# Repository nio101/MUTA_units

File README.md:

# MUTA_units
An open source home automation solution for hobbyists and makers

## customizing the firmwares before flashing

In the **MPLAB IPE**, activate *Setting/advanced mode*, open the firmware/.hex file you want to customize, and then select *View/show memory*.
On the *Operate* tab, you'll have a memory view window. Skip to the end of the memory and you fill view the constants you can edit inline before flashing:
* static_encryption_key @ 0x01FFEC (8 bytes)
* make/model @ 0x01FFF4 (2 bytes)
* unit_uid @ 0x01FFF6 (2 bytes)
You can then use the *view/fill memory* dialog to modify those values and check the modifications on the memory view afterwards.
*important: due to Endianness, the first and second bytes are swapped for each memory value, so you should input for example 0x0201@0x01FFF4 to get a 01 model and a 02 make*
*remark: This manual process could be done in a much easier way with the hexmate util, but my first tries weren't successfull and I couldn't spend more time on it.*

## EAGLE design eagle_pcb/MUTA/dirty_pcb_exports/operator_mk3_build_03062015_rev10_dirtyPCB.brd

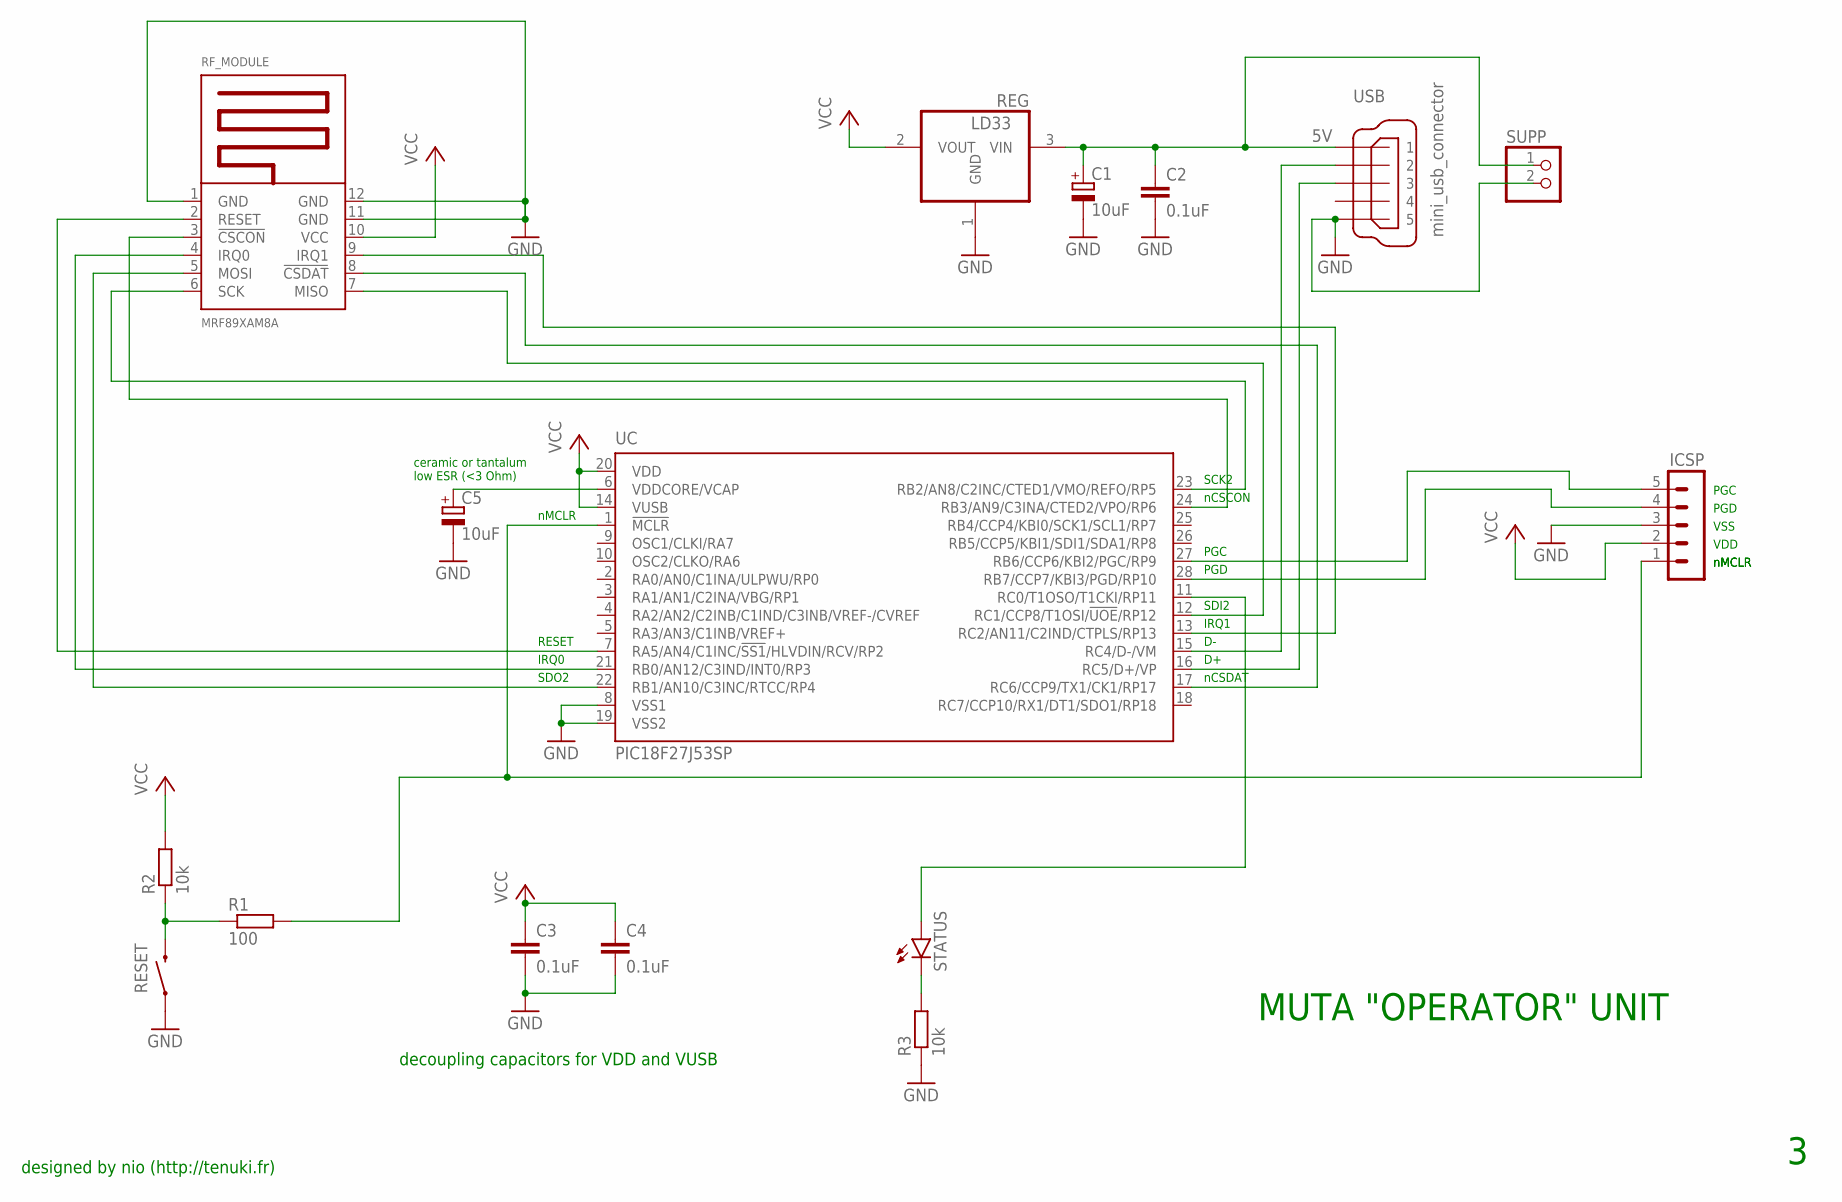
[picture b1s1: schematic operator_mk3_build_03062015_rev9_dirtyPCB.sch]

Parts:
C1: 10uF; TT5D6
C2, C3, C4: 0.1uF; C050-025X075
C5: 10uF; C/6032-28R
ICSP: MA05-1
R1: 100; 0207/10
R2: 10k; 0207/10
R3: 10k; 0207/2V
REG: LD33; SOT223; MPN LD33
RESET: SWITCH-MOMENTARY-2PTH; TACTILE-PTH
RF_MODULE: MRF89XAM8A; MRF89XAMXA
STATUS: LED5MM
SUPP: PINHD-1X2; 1X02
UC: PIC18F27J53SP; DIL28-3
USB: mini_usb_connector; UX60-MB-5ST

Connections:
5V: C1.+, C2.1, REG.3 (VIN), SUPP.1, USB.1
GND: C1.-, C2.2, C3.2, C4.2, C5.-, ICSP.3, R3.1, REG.1 (GND), RESET.1, RF_MODULE.1 (GND), RF_MODULE.11 (GND), RF_MODULE.12 (GND), SUPP.2, UC.8 (VSS1), UC.19 (VSS2), USB.5
unnamed: UC.15 (RC4/D-/VM), USB.2
unnamed: UC.16 (RC5/D+/VP), USB.3
unnamed: ICSP.1, R1.2, UC.1 (!MCLR)
unnamed: C5.+, UC.6 (VDDCORE/VCAP)
unnamed: R1.1, R2.1, RESET.3 (2)
unnamed: ICSP.4, UC.28 (RB7/CCP7/KBI3/PGD/RP10)
unnamed: ICSP.5, UC.27 (RB6/CCP6/KBI2/PGC/RP9)
unnamed: RF_MODULE.2 (RESET), UC.7 (RA5/AN4/C1INC/!SS1!/HLVDIN/RCV/RP2)
unnamed: RF_MODULE.6 (SCK), UC.23 (RB2/AN8/C2INC/CTED1/VMO/REFO/RP5)
unnamed: R3.2, STATUS.K (C)
unnamed: STATUS.A, UC.11 (RC0/T1OSO/T1CKI/RP11)
unnamed: RF_MODULE.7 (MISO), UC.12 (RC1/CCP8/T1OSI/!UOE!/RP12)
unnamed: RF_MODULE.3 (!CSCON), UC.24 (RB3/AN9/C3INA/CTED2/VPO/RP6)
unnamed: RF_MODULE.5 (MOSI), UC.22 (RB1/AN10/C3INC/RTCC/RP4)
unnamed: RF_MODULE.4 (IRQ0), UC.21 (RB0/AN12/C3IND/INT0/RP3)
unnamed: RF_MODULE.9 (IRQ1), UC.13 (RC2/AN11/C2IND/CTPLS/RP13)
unnamed: RF_MODULE.8 (!CSDAT), UC.17 (RC6/CCP9/TX1/CK1/RP17)
VCC: C3.1, C4.1, ICSP.2, R2.2, REG.2 (VOUT), RF_MODULE.10 (VCC), UC.14 (VUSB), UC.20 (VDD)

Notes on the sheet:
MUTA "OPERATOR" UNIT
decoupling capacitors for VDD and VUSB
ceramic or tantalum low ESR (<3 Ohm)
nMCLR
VDD
VSS
PGD
PGC
SCK2
SDI2
SDO2
IRQ1
IRQ0
nCSDAT
nCSCON
RESET
designed by nio (http://tenuki.fr)

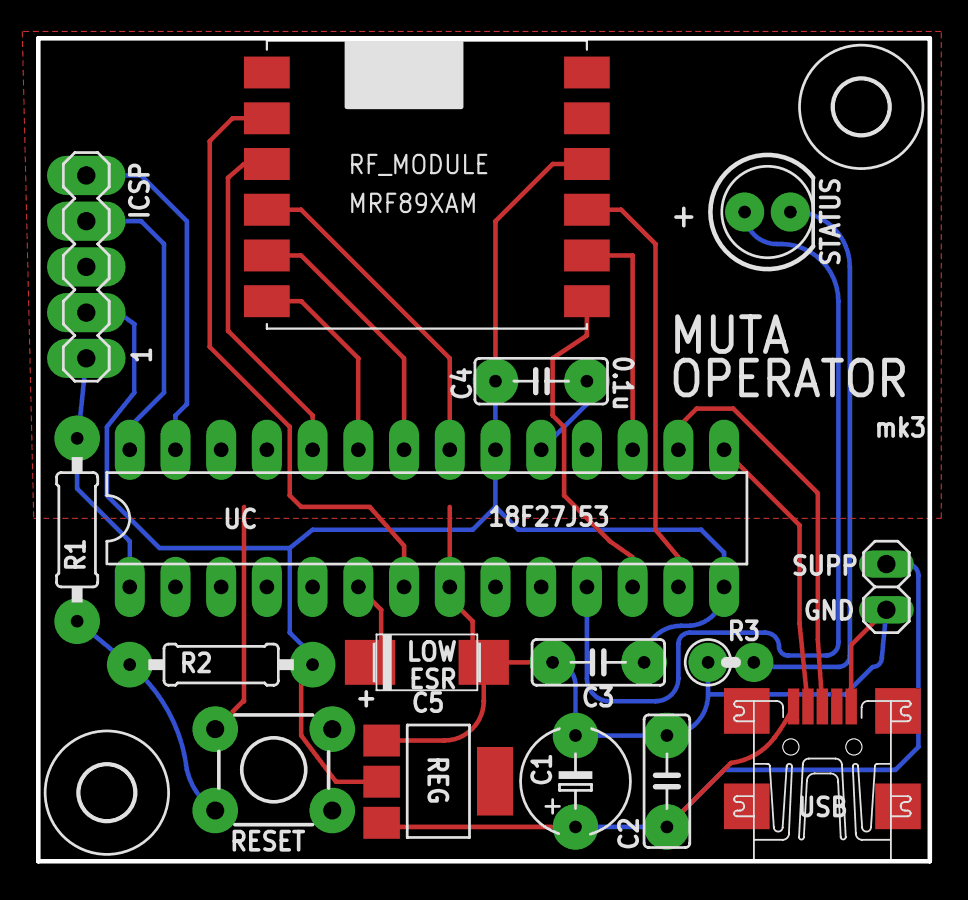
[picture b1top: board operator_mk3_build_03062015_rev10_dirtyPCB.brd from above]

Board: 2 copper layers, 49.5 x 45.7 mm, 18 parts (0 on the bottom side), 20 nets.

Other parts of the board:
U$1, U$4: 3,0

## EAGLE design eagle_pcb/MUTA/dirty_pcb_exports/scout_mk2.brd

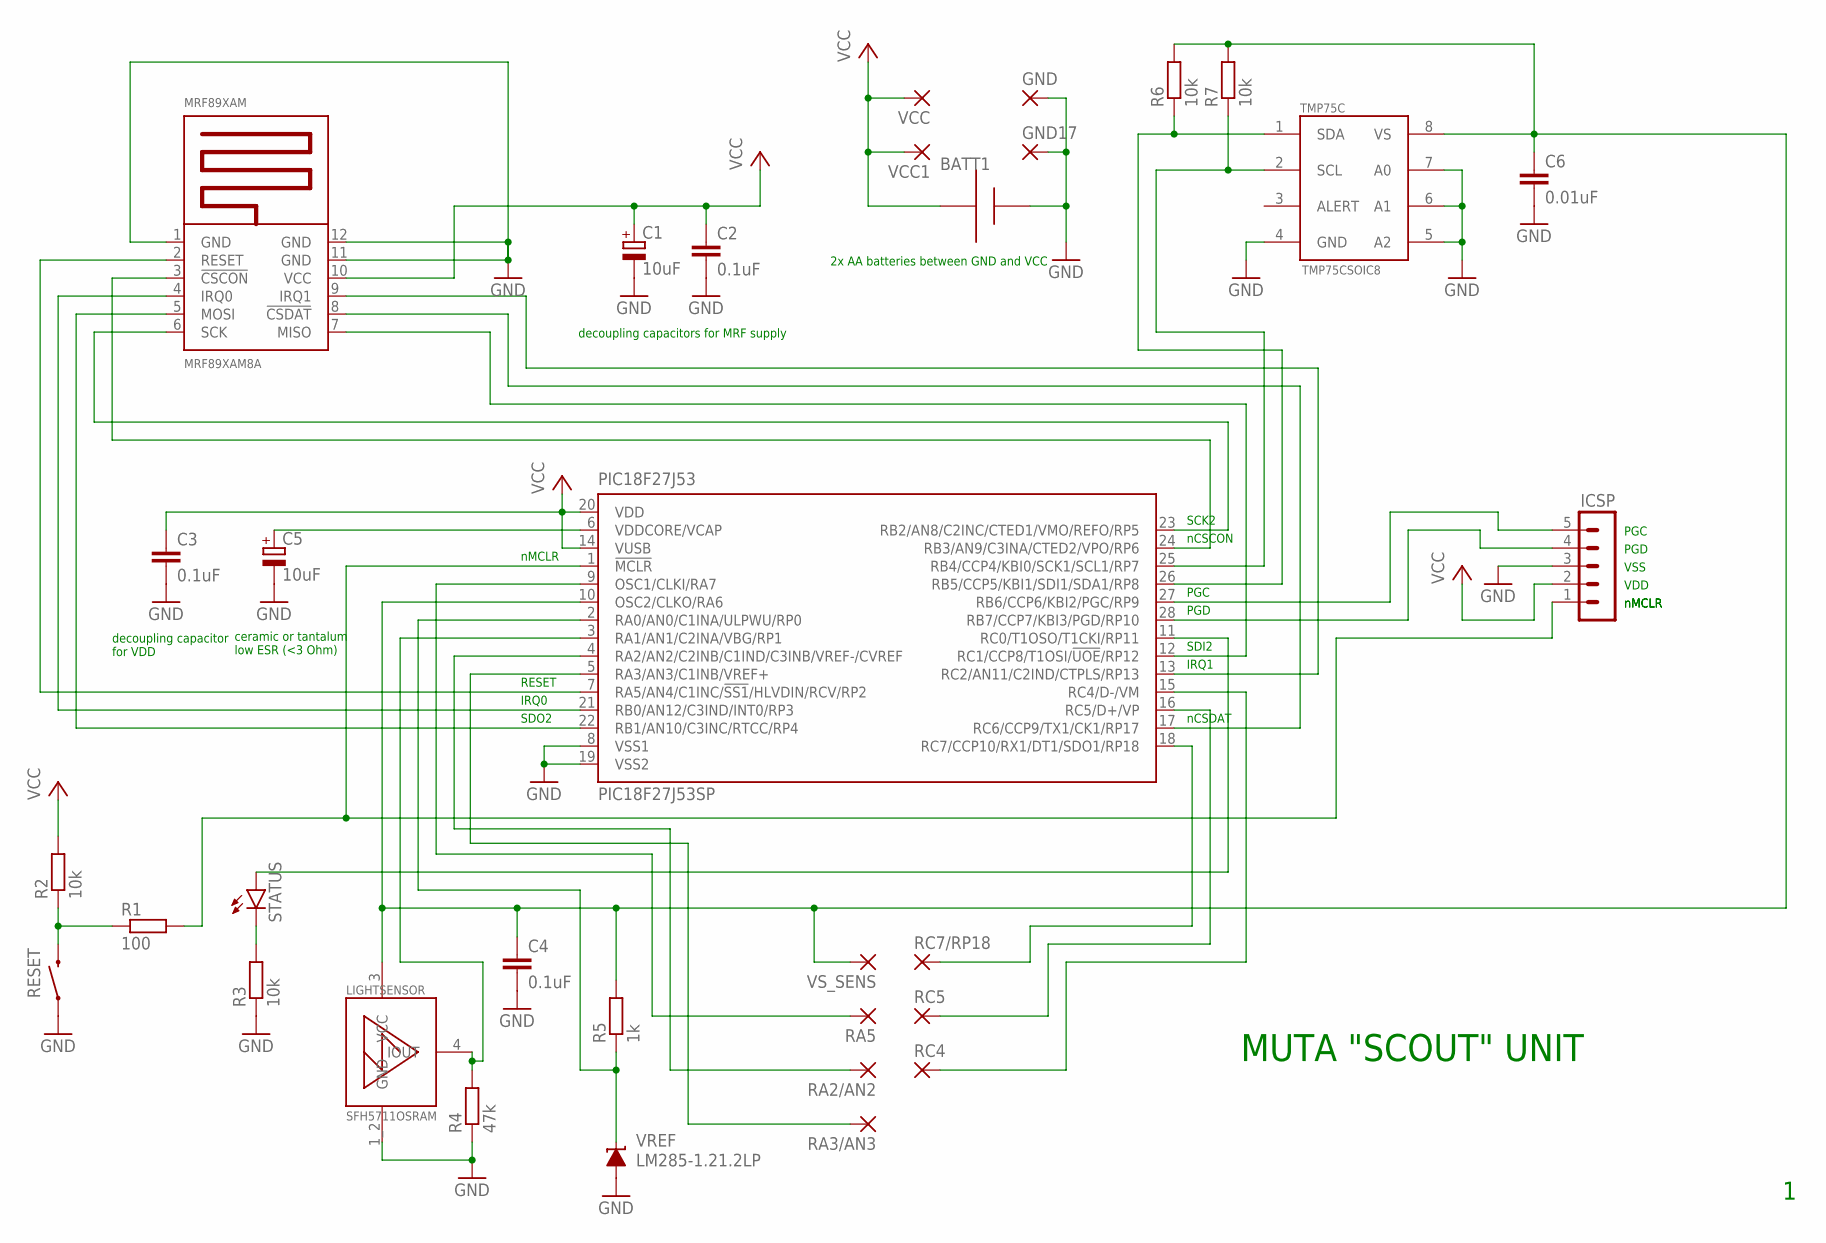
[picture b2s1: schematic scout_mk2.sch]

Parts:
BATT1: AAA; 2XAAA
C1: 10uF; TT5D6
C2, C3, C4: 0.1uF; C050-025X075
C5: 10uF; C/6032-28R
C6: 0.01uF; C050-025X075
GND, GND17: 3,81/1,1
ICSP: MA05-1
LIGHTSENSOR: SFH5711OSRAM; SFH5711
MRF89XAM: MRF89XAM8A; MRF89XAMXA
PIC18F27J53: PIC18F27J53SP; DIL28-3
R1: 100; 0207/10
R2, R6, R7: 10k; 0207/10
R3: 10k; 0207/2V
R4: 47k; 0207/10
R5: 1k; 0207/10
RA2/AN2, RA3/AN3, RA5: 3,81/1,1
RC4, RC5, RC7/RP18: 3,81/1,1
RESET: SWITCH-MOMENTARY-2PTH; TACTILE-PTH
STATUS: LED1206; LED-1206
TMP75C: TMP75CSOIC8; SOIC8
VCC, VCC1: 3,81/1,1
VREF: LM285-1.21.2LP; LP_O-PBCY-W3
VS_SENS: 3,81/1,1

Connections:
GND: BATT1.P$1 (+), C1.-, C2.2, C3.2, C4.2, C5.-, C6.2, GND.1, GND17.1, ICSP.3, LIGHTSENSOR.1_2 (GND), MRF89XAM.1 (GND), MRF89XAM.11 (GND), MRF89XAM.12 (GND), PIC18F27J53.8 (VSS1), PIC18F27J53.19 (VSS2), R3.1, R4.1, RESET.1, TMP75C.4 (GND), TMP75C.5 (A2), TMP75C.6 (A1), TMP75C.7 (A0), VREF.3 (A)
unnamed: LIGHTSENSOR.4 (IOUT), PIC18F27J53.3 (RA1/AN1/C2INA/VBG/RP1), R4.2
unnamed: ICSP.1, PIC18F27J53.1 (!MCLR), R1.2
unnamed: C5.+, PIC18F27J53.6 (VDDCORE/VCAP)
unnamed: R1.1, R2.1, RESET.3 (2)
unnamed: ICSP.4, PIC18F27J53.28 (RB7/CCP7/KBI3/PGD/RP10)
unnamed: ICSP.5, PIC18F27J53.27 (RB6/CCP6/KBI2/PGC/RP9)
unnamed: PIC18F27J53.2 (RA0/AN0/C1INA/ULPWU/RP0), R5.1, VREF.2 (C)
unnamed: MRF89XAM.2 (RESET), PIC18F27J53.7 (RA5/AN4/C1INC/!SS1!/HLVDIN/RCV/RP2)
unnamed: MRF89XAM.6 (SCK), PIC18F27J53.23 (RB2/AN8/C2INC/CTED1/VMO/REFO/RP5)
unnamed: PIC18F27J53.26 (RB5/CCP5/KBI1/SDI1/SDA1/RP8), R6.1, TMP75C.1 (SDA)
unnamed: PIC18F27J53.25 (RB4/CCP4/KBI0/SCK1/SCL1/RP7), R7.1, TMP75C.2 (SCL)
unnamed: PIC18F27J53.9 (OSC1/CLKI/RA7), RA5.1
unnamed: R3.2, STATUS.C
unnamed: PIC18F27J53.11 (RC0/T1OSO/T1CKI/RP11), STATUS.A
unnamed: PIC18F27J53.4 (RA2/AN2/C2INB/C1IND/C3INB/VREF-/CVREF), RA2/AN2.1
unnamed: PIC18F27J53.5 (RA3/AN3/C1INB/VREF+), RA3/AN3.1
unnamed: MRF89XAM.7 (MISO), PIC18F27J53.12 (RC1/CCP8/T1OSI/!UOE!/RP12)
unnamed: MRF89XAM.3 (!CSCON), PIC18F27J53.24 (RB3/AN9/C3INA/CTED2/VPO/RP6)
unnamed: MRF89XAM.5 (MOSI), PIC18F27J53.22 (RB1/AN10/C3INC/RTCC/RP4)
unnamed: MRF89XAM.4 (IRQ0), PIC18F27J53.21 (RB0/AN12/C3IND/INT0/RP3)
unnamed: MRF89XAM.9 (IRQ1), PIC18F27J53.13 (RC2/AN11/C2IND/CTPLS/RP13)
unnamed: MRF89XAM.8 (!CSDAT), PIC18F27J53.17 (RC6/CCP9/TX1/CK1/RP17)
unnamed: PIC18F27J53.18 (RC7/CCP10/RX1/DT1/SDO1/RP18), RC7/RP18.1
unnamed: PIC18F27J53.16 (RC5/D+/VP), RC5.1
unnamed: PIC18F27J53.15 (RC4/D-/VM), RC4.1
unnamed: C4.1, C6.1, LIGHTSENSOR.3 (VCC), PIC18F27J53.10 (OSC2/CLKO/RA6), R5.2, R6.2, R7.2, TMP75C.8 (VS), VS_SENS.1
VCC: BATT1.P$2 (-), C1.+, C2.1, C3.1, ICSP.2, MRF89XAM.10 (VCC), PIC18F27J53.14 (VUSB), PIC18F27J53.20 (VDD), R2.2, VCC.1, VCC1.1

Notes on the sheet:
MUTA "SCOUT" UNIT
decoupling capacitor for VDD
ceramic or tantalum low ESR (<3 Ohm)
nMCLR
VDD
VSS
PGD
PGC
SCK2
SDI2
SDO2
IRQ1
IRQ0
nCSDAT
nCSCON
RESET
decoupling capacitors for MRF supply
2x AA batteries between GND and VCC

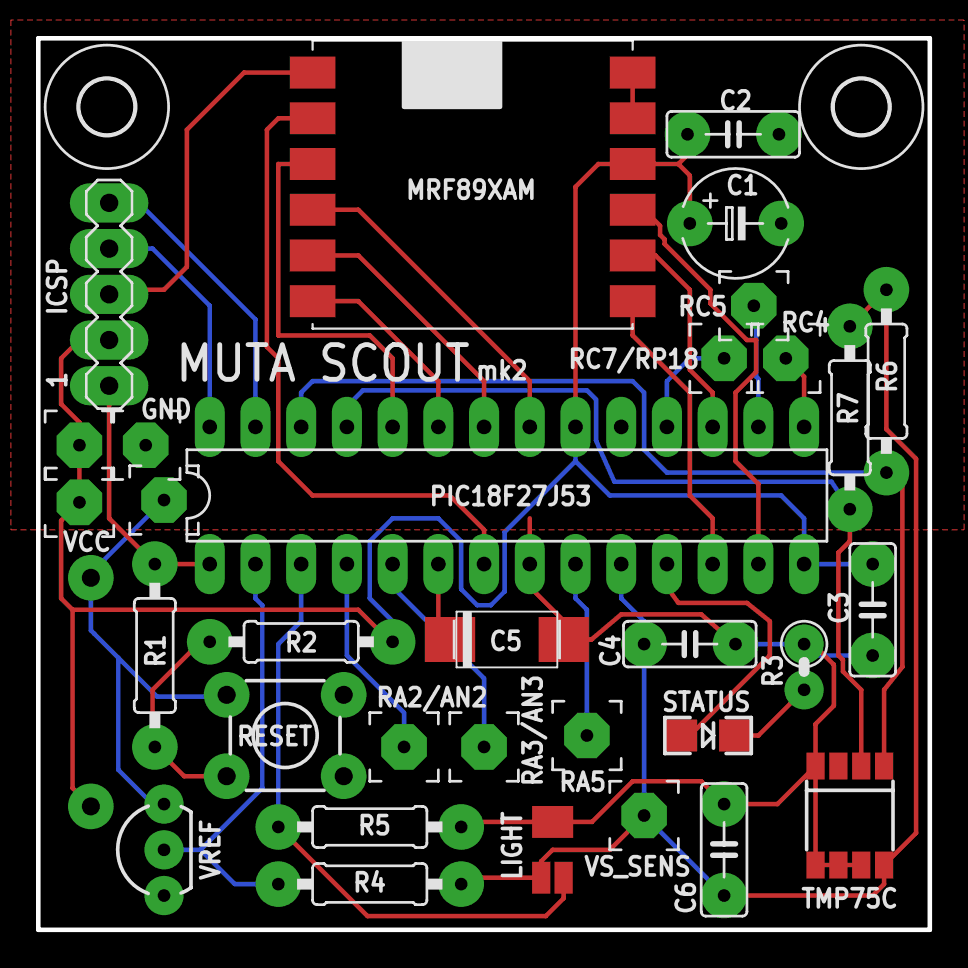
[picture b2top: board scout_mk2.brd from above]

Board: 2 copper layers, 49.5 x 49.5 mm, 35 parts (0 on the bottom side), 28 nets.

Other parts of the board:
U$2, U$3: 3,0

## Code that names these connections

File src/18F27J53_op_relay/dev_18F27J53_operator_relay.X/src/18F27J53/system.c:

/********************************************************************
 Software License Agreement:

 The software supplied herewith by Microchip Technology Incorporated
 (the "Company") for its PIC(R) Microcontroller is intended and
 supplied to you, the Company's customer, for use solely and
 exclusively on Microchip PIC Microcontroller products. The
 software is owned by the Company and/or its supplier, and is
 protected under applicable copyright laws. All rights are reserved.
 Any use in violation of the foregoing restrictions may subject the
 user to criminal sanctions under applicable laws, as well as to
 civil liability for the breach of the terms and conditions of this
 license.

 THIS SOFTWARE IS PROVIDED IN AN "AS IS" CONDITION. NO WARRANTIES,
 WHETHER EXPRESS, IMPLIED OR STATUTORY, INCLUDING, BUT NOT LIMITED
 TO, IMPLIED WARRANTIES OF MERCHANTABILITY AND FITNESS FOR A
 PARTICULAR PURPOSE APPLY TO THIS SOFTWARE. THE COMPANY SHALL NOT,
 IN ANY CIRCUMSTANCES, BE LIABLE FOR SPECIAL, INCIDENTAL OR
 CONSEQUENTIAL DAMAGES, FOR ANY REASON WHATSOEVER.
 *******************************************************************/
#include "system.h"
#include "system_config.h"
#include "plib/rtcc.h"

// ---------------------------------------------------------------
// PIC18F27J53 Configuration

#pragma config WDTEN = OFF      // Watchdog Timer (Disabled - Controlled by SWDTEN bit)
#pragma config CFGPLLEN = OFF    // PLL Enable Configuration Bit (PLL Disabled)
#pragma config STVREN = OFF     // Stack Overflow/Underflow Reset (Disabled)
#pragma config XINST = OFF       // Extended Instruction Set (Disabled)
#pragma config CP0 = OFF        // Code Protect (Program memory is not code-protected)
#pragma config OSC = INTOSC     // internal oscillator without PLL
#pragma config CLKOEC = OFF     // EC Clock Out Enable Bit  (CLKO output disabled on the RA6 pin)
#pragma config FCMEN = OFF      // Fail-Safe Clock Monitor (Disabled)
#pragma config IESO = OFF           // Internal External Oscillator Switch Over Mode (Disabled)
#pragma config RTCOSC = INTOSCREF   // RTCC Clock Select (RTCC uses INTRC)
#pragma config ADCSEL = BIT12       // 12 - Bit ADC Enabled

/*********************************************************************
 * Function:        void SYSTEM_Initialize( void )
 *
 * PreCondition:    None
 *
 * Input:           None
 *
 * Output:          None
 *
 * Side Effects:    Board is initialized for P2P usage
 *
 * Overview:        This function configures the board 
 *
 * Note:            This routine needs to be called before the function 
 *                  to initialize stack or any other function that
 *                  operates on the stack
 ********************************************************************/
void SYSTEM_Initialize(void)
{    
    // No PLL
    PLLEN = 0;

    // 8MHz from INTOSC
    OSCCONbits.IRCF = 0b111;

    // no analog pin used, all digital
    ANCON0 = 0xFF;
    ANCON1 = 0x1F;

    // configure IO as OUTPUT => 0uA mesuré en sleep !!!
    TRISA = 0;
    TRISB = 0;
    TRISC = 0;    

    LATCbits.LATC0 = 1;     // turn off the LED!

    UPUEN = 0;  // USB internal pullup disabled
    UCONbits.USBEN = 0; // USB disabled    

    // turn RTCC and RTCC/alarm ON
    //RtccInitClock();   // config says RTCC should use INTRC
                         // RtccInitClock enables timer1 crystal use!
    RTCCFG = 0x0;
    RTCCAL = 0x00;  // signed value to calibrate RTCC on INTOSC
    /*if(mRtccIsOn()) // - not necessary!
    {
       if(!mRtccIsWrEn())
       {
           RtccWrOn();
       }
       mRtccOff();
    }*/
    mRtccWrOff();
    RtccWrOn(); //write enable the rtcc registers
    mRtccOn(); //enable the rtcc module
    mRtccAlrmEnable(); //enable the rtcc alarm
    RTCCFGbits.RTCPTR0 = 0; //RTCVALH/L will point to min/seconds values
    RTCCFGbits.RTCPTR1 = 0;
    RTCVALHbits.RTCVALH = 0x00; // write 00 to min & sec
    RTCVALLbits.RTCVALL = 0x00;
    // RTCC alarm setup
    ALRMCFGbits.AMASK = 0b0011; // alarm every minute
    //ALRMCFGbits.AMASK = 0b0010; // alarm every 10sec
    ALRMCFGbits.CHIME = 1;      // chime ON, alarm is repeated indefinitly
    ALRMCFGbits.ALRMEN = 1;     // Alarm ON
    mRtccWrOff();   // write disable rtcc regs

    // setup RTCC interrupt
    IPR3bits.RTCCIP = 0; // low priority for RTCC
    PIR3bits.RTCCIF = 0;  // clear RTCC interrupt flag
    PIE3bits.RTCCIE = 1;  // RTCC interrupt enable

    /*******************************************************************/
    // Configure PPS Related Pins
    /*******************************************************************/
    // Unlock to config PPS
    EECON2 = 0x55;
    EECON2 = 0xAA;
    PPSCONbits.IOLOCK = 0;

    // inputs
    RPINR1 = 13;    // Mapping IRQ1 to RC2(RP13)
    RPINR21 = 12;   // Mapping SDI2 to RC1(RP12)    
    RPINR22 = 5;    // Mapping SCK2IN to RB2(RP5)

    // outputs
    RPOR4 = 10;     // Mapping SDO2 to RB1(RP4)
    RPOR5 = 11;     // Mapping SCK2OUT to RB2(RP5)
    RPOR11 = 14;  // RC0/RP11: ICCP1 output (for pwm led)

    // Lock System
    EECON2 = 0x55;
    EECON2 = 0xAA;
    PPSCONbits.IOLOCK = 1;

    /*******************************************************************/
    // Config RF Radio
    /*******************************************************************/

    RCONbits.IPEN = 1;  // enable interrupt priorities management

    /*******************************************************************/
    // Config MRF89XA Pins
    /*******************************************************************/

    Data_nCS = 1;
    Config_nCS = 1;
    
    Data_nCS_TRIS = 0; 
    Config_nCS_TRIS = 0;   

    // INT0/INT1 config pin as input
    IRQ0_INT_TRIS = 1;
    IRQ1_INT_TRIS = 1;
    
    // Config IRQ1 Edge = Rising
    INTCON2bits.INTEDG1 = 1;
    
    // Config IRQ0 Edge = Rising
    INTCON2bits.INTEDG0 = 1;
    
    PHY_IRQ0 = 0;           // MRF89XA
    PHY_IRQ0_En = 1;        // INT0 enable (INT0:always high priority)

    PHY_IRQ1 = 0;           // MRF89XA
    PHY_IRQ1_IP = 1;        // INT1 => High Priority interrupt
    PHY_IRQ1_En = 1;        // MRF89XA

    /*******************************************************************/
    // Configure SPI2
    /*******************************************************************/

    SDI_TRIS = 1;
    SDO_TRIS = 0;
    SCK_TRIS = 0;
    
    SSP2STAT = 0xC0; // 1100 0000
    SSP2CON1 = 0b00101010;  // Fosc/8 => SPI@1MHz / this enables SSP1 too
    //SSP2CON1 = 0x21; // 0010 0001 - Fosc / 16 => SPI@1MHz if FOSC@16MHz
    //SSP2CON1 = 0x22;  // Fosc / 64

    PHY_RESETn = 0;         // No reset
    PHY_RESETn_TRIS = 1;    // !?! should be an output here: reset unused !?!

    /*******************************************************************/
    // Enable System Interupts
    /*******************************************************************/
    INTCONbits.GIEH = 1;
    INTCONbits.GIEL = 1;    
    
    /*******************************************************************/
    // Configure LED PWM & timer
    /*******************************************************************/   
    
    // setup CCP1 PWM to drive led on RC0/RP11
    // PPS: already assigned CCP1 to RC0/RP11
#ifdef MK1
    TRISCbits.TRISC6 = 1; // RC6 => input (PWM LED OFF) (mk1 only)
#else #ifdef MK3
    TRISCbits.TRISC0 = 1; // RC0 => input (PWM LED OFF) (mk3 and +)
#endif    

    CCPTMRS0 = 0x00; //select timer resources, Timer2 for CCP1 (and /2/3)

    PR2 = 0xF9; // load with PWM period value (fixed at 1 kHz)
    CCP1CONbits.DC1B = 0b00;    // least significant bits of duty cycle
    CCP1CONbits.CCP1M = 0b1100; // PWM mode
    CCPR1L = 0x00; // eight high bits of duty cycle

    T2CONbits.T2CKPS = 0b10; // timer2 prescale: /16
    T2CONbits.TMR2ON = 0b1;  // timer2 ON

#ifdef MK1
    TRISCbits.TRISC6 = 0; // RC6 => output (PWM LED ON) (mk1 only)
#else #ifdef MK3
    TRISCbits.TRISC0 = 0; // RC0 => output (PWM LED ON) (mk3 and +)
#endif    
    // duty cycle is zero here so the LED *should* be OFF
    
    // setup timer4 to update the LED brightness every 5ms (via interrupt)
    T4CONbits.T4OUTPS = 0b1111; // :16 postscaler
    T4CONbits.T4CKPS = 0b11;    // :16 prescaler
    PR4 = 234;             // period for an interrupt every 30ms@8MHz
    IPR3bits.TMR4IP = 0;    // interrupt for timer4 is low priority
    PIR3bits.TMR4IF = 0;    // clear flag
    PIE3bits.TMR4IE = 1;    // enable interrupt    
    T4CONbits.TMR4ON = 1; // timer4 is ON    
}

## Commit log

2016-08-13 added explanations about compiler+lib requirements for compiling source code
2016-08-13 source code comments
2016-08-14 minor fixes, now every unit emits at full power at startup, TODO list and README.md
2016-12-04 operator updated for muta v01
2016-12-09 muta v01 scout ok
2016-12-09 rtcc reset added
2016-12-10 cleaned all the sleep cycles for the scout
2016-12-29 fixed _signed bug for temp

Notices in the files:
eagle_pcb/MUTA/dirty_pcb_exports/operator_mk3_build_03062015_rev10_dirtyPCB.brd:
Designed by nio101 (http://tenuki.fr) - CC BY-SA
parts and their libraries:
SparkFun-LED: Licensing: Creative Commons ShareAlike 4.0 International - https://creativecommons.org/licenses/by-sa/4.0
